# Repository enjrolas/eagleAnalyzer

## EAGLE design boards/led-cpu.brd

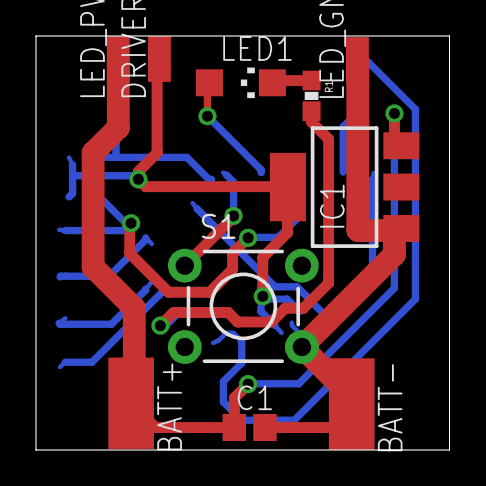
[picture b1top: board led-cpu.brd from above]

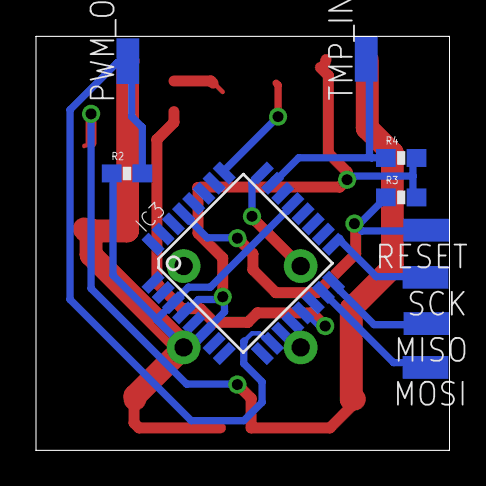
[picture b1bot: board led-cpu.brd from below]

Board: 2 copper layers, 23.0 x 23.0 mm, 20 parts (10 on the bottom side), 13 nets.

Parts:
BATT+: SMD2,54-5,08
BATT-: SMD2,54-5,08
C1: 0.1uF; C0805
DRIVER_PWR: SMD1,27-2,54
IC1: LD117AS50TR; SOT223
IC3: MEGA8-AI; TQFP32-08
LED1: D1; CHIPLED_1206
LED_GND: SMD1,27-2,54
LED_PWR: SMD1,27-2,54
MISO: MISO; SMD1,27-2,54
MOSI: MOSI; SMD1,27-2,54
PWM_OUT: SMD1,27-2,54
R1: 33; 0603-RES
R2, R3: 10k; 0603-RES
R4: 2k7; 0603-RES
RESET: SMD1,27-2,54
S1: TACTILE-PTH
SCK: SCK; SMD1,27-2,54
TMP_IN: SMD1,27-2,54

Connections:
IND_LED_A: IC3.25, LED1.A
IND_LED_B: IC3.13, R1.2
LED_GND: BATT-.1, C1.2, IC1.1, IC3.3, IC3.5, IC3.21, LED_GND.1, R2.1, S1.4
MISO: IC3.16, MISO.1
MOSI: IC3.15, MOSI.1
unnamed: LED1.C, R1.1
unnamed: BATT+.1, C1.1, IC1.3, LED_PWR.1
PWM_OUT: IC3.10, PWM_OUT.1, R2.2
PWR_SW: IC3.24, S1.1
RESET: IC3.29, R3.1, RESET.1
SCK: IC3.17, SCK.1
TMP_IN: IC3.23, R4.1, TMP_IN.1
VCC: DRIVER_PWR.1, IC1.4, IC3.4, IC3.6, R3.2, R4.2

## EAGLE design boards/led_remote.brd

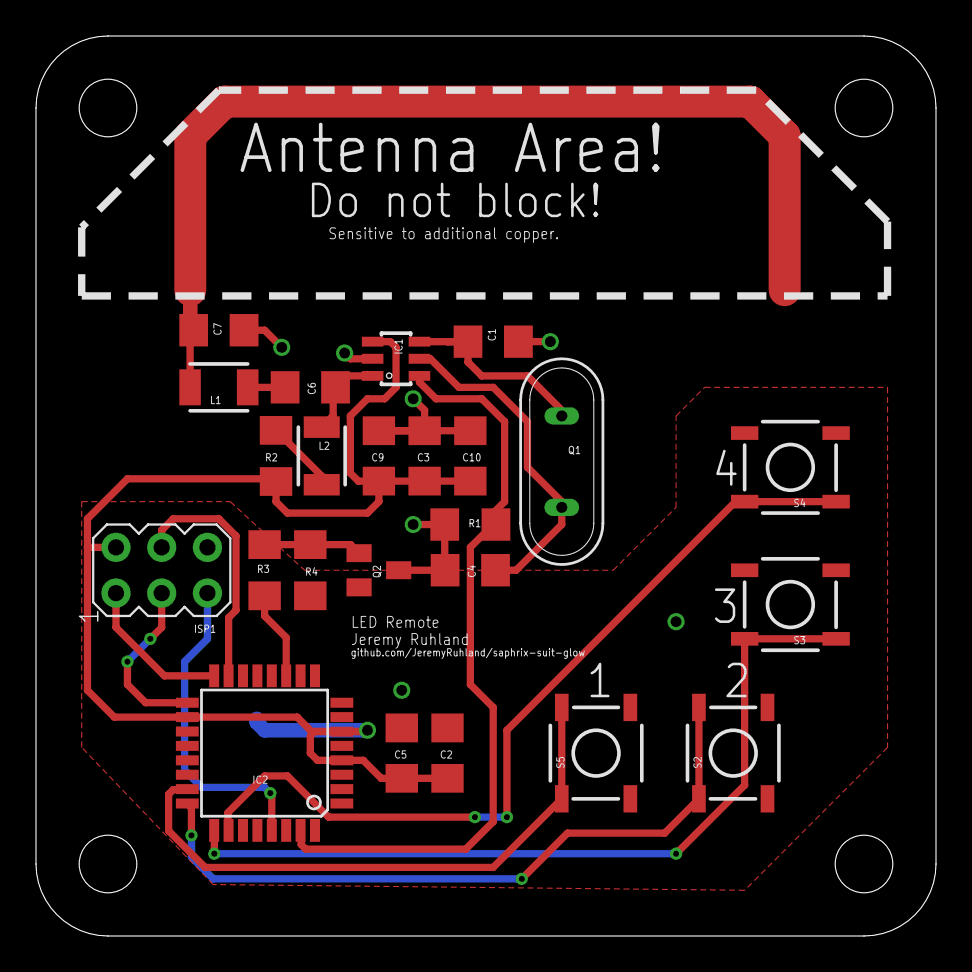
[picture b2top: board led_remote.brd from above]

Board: 2 copper layers, 50.0 x 50.0 mm, 26 parts (1 on the bottom side), 20 nets.

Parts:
C1, C4: 18pf; C1206
C2, C9: 10uf; C1206
C3, C5: 0.1uf; C1206
C6: 12pf; C1206
C7: 4.7pf; C1206
C10: 100pf; C1206
G1: BATTCON_20MM
IC1: MICRF113; SOT23-6
IC2: MEGA8-AI; TQFP32-08
ISP1: AVRISP-6; AVRISP
L1: 1210
L2: 470nh; 1210
PCB2: PCB_DP_SQUARE-5X5; DP5050_V1
Q1: 13.56mhz; QS
Q2: SOT23
R1, R4: 100k; R1206
R2: R1206
R3: 100; R1206
S2, S3, S4, S5: TACTILE_SWITCH_SMD

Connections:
AGND: C1.2, C3.2, C4.2, C7.2, C9.2, C10.2, IC1.2, Q2.3, R1.1
ANT: C7.1, L1.2
GND: C2.2, C5.2, G1.2, IC2.3, IC2.5, IC2.21, ISP1.6, Q2.2, R4.1, S2.3, S2.4, S3.3, S3.4, S4.3, S4.4, S5.3, S5.4
MISO: IC2.16, ISP1.1
MOSI: IC2.15, ISP1.4
unnamed: L2.1, R2.1
unnamed: Q2.1, R3.1, R4.2
unnamed: C1.1, IC1.4, Q1.1
unnamed: C4.1, IC1.5, Q1.2
unnamed: IC2.26, S4.1, S4.2
unnamed: C6.1, IC1.1, L2.2
unnamed: C6.2, L1.1
unnamed: IC2.23, S5.1, S5.2
unnamed: IC2.24, S2.1, S2.2
unnamed: IC2.25, S3.1, S3.2
RST: IC2.29, ISP1.5
SCK: IC2.17, ISP1.3
TX: IC1.6, IC2.31, R1.2
TXPWR: IC2.11, R3.2
VCC: C2.1, C3.1, C5.1, C9.1, C10.1, G1.1, IC1.3, IC2.4, IC2.6, IC2.18, ISP1.2, R2.2

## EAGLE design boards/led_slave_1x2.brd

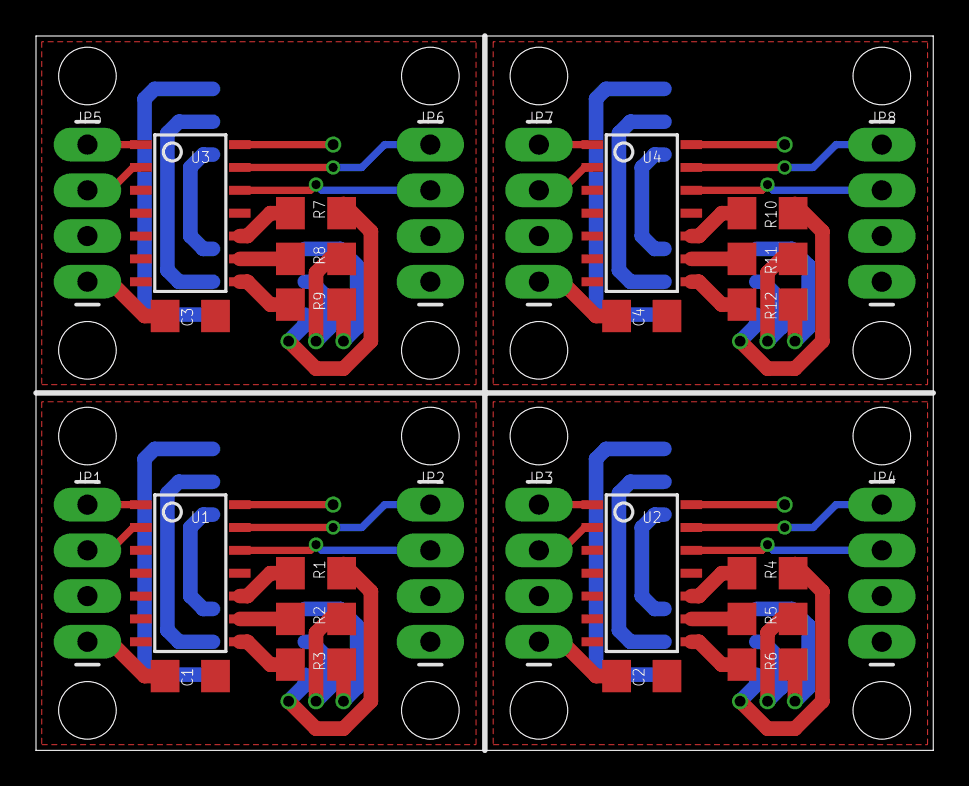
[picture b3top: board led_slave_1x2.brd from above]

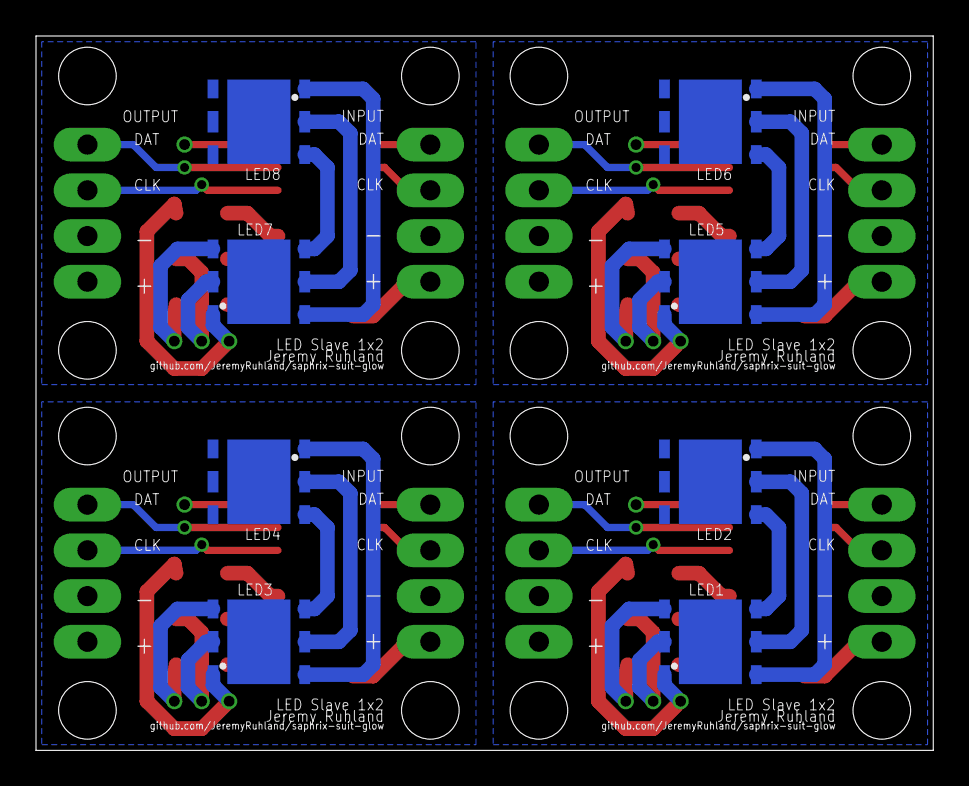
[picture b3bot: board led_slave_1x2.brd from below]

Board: 2 copper layers, 49.8 x 39.7 mm, 36 parts (8 on the bottom side), 60 nets.

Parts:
C1, C2, C3, C4: C1206
JP1, JP2, JP3, JP4, JP5, JP6, JP7, JP8: 1X04_LONGPADS
LED1, LED2, LED3, LED4, LED5, LED6, LED7, LED8: F50360
R1, R2, R3, R4, R5, R6, R7, R8, R9, R10, R11, R12: R1206
U1, U2, U3, U4: WS2801; SOP-14

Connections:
unnamed: JP1.3, U1.2
unnamed: JP1.4, U1.1
unnamed: JP2.4, U1.13
unnamed: JP2.3, U1.12
unnamed: R1.2, U1.10
unnamed: R2.2, U1.9
unnamed: R3.2, U1.8
unnamed: JP4.4, U2.13
unnamed: JP4.3, U2.12
unnamed: LED3.BA, LED4.BC
unnamed: LED1.BC, R3.1
unnamed: LED1.GC, R2.1
unnamed: LED3.GA, LED4.GC
unnamed: LED3.RA, LED4.RC
unnamed: LED1.BA, LED2.BC
unnamed: LED1.GA, LED2.GC
unnamed: LED1.RA, LED2.RC
unnamed: R4.2, U2.10
unnamed: R5.2, U2.9
unnamed: R6.2, U2.8
unnamed: LED1.RC, R1.1
unnamed: LED3.BC, R6.1
unnamed: LED3.GC, R5.1
unnamed: LED3.RC, R4.1
unnamed: JP3.3, U2.2
unnamed: C1.1, JP1.1, JP2.1, LED2.BA, LED2.GA, LED2.RA, U1.14
unnamed: C1.2, JP1.2, JP2.2, U1.4, U1.5, U1.6, U1.7
unnamed: JP3.4, U2.1
unnamed: C2.1, JP3.1, JP4.1, LED4.BA, LED4.GA, LED4.RA, U2.14
unnamed: C2.2, JP3.2, JP4.2, U2.4, U2.5, U2.6, U2.7
unnamed: JP6.4, U3.13
unnamed: JP6.3, U3.12
unnamed: LED5.BA, LED6.BC
unnamed: LED5.GA, LED6.GC
unnamed: LED5.RA, LED6.RC
unnamed: R7.2, U3.10
unnamed: R8.2, U3.9
unnamed: R9.2, U3.8
unnamed: LED5.BC, R9.1
unnamed: LED5.GC, R8.1
unnamed: LED5.RC, R7.1
unnamed: JP5.3, U3.2
unnamed: JP5.4, U3.1
unnamed: C3.1, JP5.1, JP6.1, LED6.BA, LED6.GA, LED6.RA, U3.14
unnamed: C3.2, JP5.2, JP6.2, U3.4, U3.5, U3.6, U3.7
unnamed: JP8.4, U4.13
unnamed: JP8.3, U4.12
unnamed: LED7.BA, LED8.BC
unnamed: LED7.GA, LED8.GC
unnamed: LED7.RA, LED8.RC
unnamed: R10.2, U4.10
unnamed: R11.2, U4.9
unnamed: R12.2, U4.8
unnamed: LED7.BC, R12.1
unnamed: LED7.GC, R11.1
unnamed: LED7.RC, R10.1
unnamed: JP7.3, U4.2
unnamed: JP7.4, U4.1
unnamed: C4.1, JP7.1, JP8.1, LED8.BA, LED8.GA, LED8.RA, U4.14
unnamed: C4.2, JP7.2, JP8.2, U4.4, U4.5, U4.6, U4.7

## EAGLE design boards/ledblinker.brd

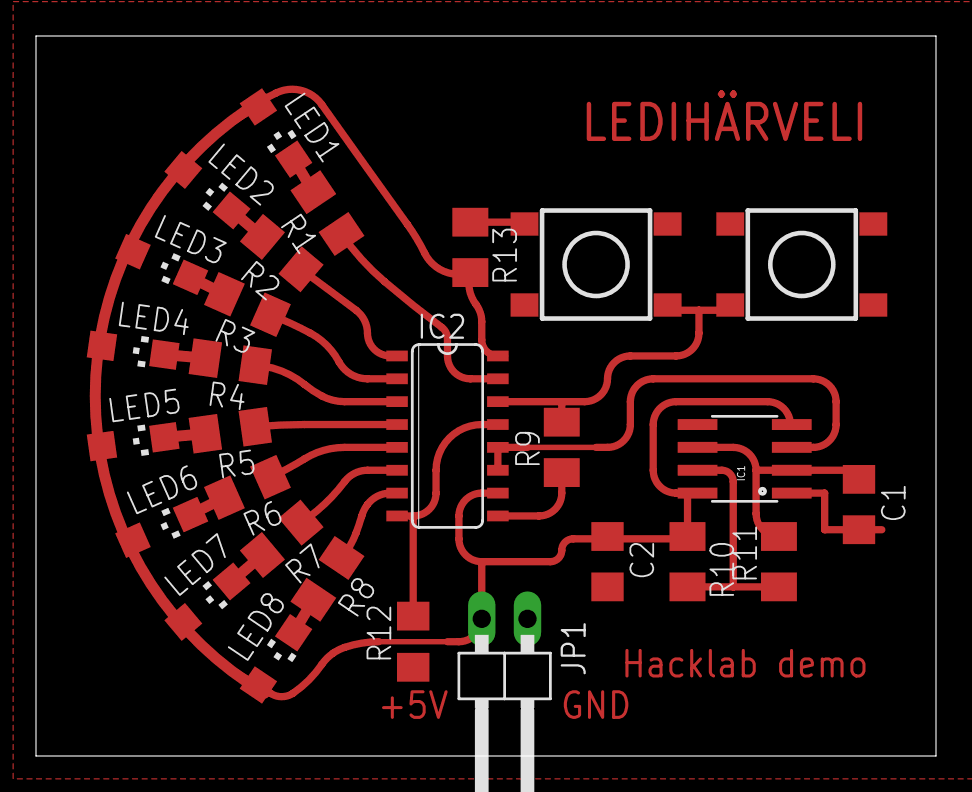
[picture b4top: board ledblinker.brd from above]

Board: 2 copper layers, 50.0 x 40.0 mm, 28 parts (0 on the bottom side), 25 nets.

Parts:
C1, C2: 100nF; C1206
IC1: NE555D; SO08
IC2: 74LS595D; SO16
JP1: 1X02/90
LED1, LED2, LED3, LED4, LED5, LED6, LED7, LED8: CHIPLED_1206
R1, R2, R3, R4, R5, R6, R7, R8: 220; M1206
R9: 22k; M1206
R10: 220k; M1206
R11: 2.2M; M1206
R12: 0R; R1206
R13: 1k; M1206
S1, S3: TACTILE_SWITCH_TALL

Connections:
GND: C1.2, C2.2, IC1.1, JP1.1, R12.1, S1.1, S1.2
unnamed: IC2.15, R1.1
unnamed: IC2.1, R2.1
unnamed: IC2.2, R3.1
unnamed: IC2.3, R4.1
unnamed: IC2.4, R5.1
unnamed: IC2.5, R6.1
unnamed: IC2.6, R7.1
unnamed: IC2.7, R8.1
unnamed: IC2.9, R9.1
unnamed: IC2.14, R9.2, S1.3, S3.1
unnamed: C1.1, IC1.2, IC1.6, R11.2
unnamed: IC1.3, IC2.11, IC2.12
unnamed: IC1.7, R10.2, R11.1
unnamed: LED1.C, R1.2
unnamed: LED2.C, R2.2
unnamed: LED3.C, R3.2
unnamed: LED4.C, R4.2
unnamed: LED5.C, R5.2
unnamed: LED6.C, R6.2
unnamed: LED7.C, R7.2
unnamed: LED8.C, R8.2
unnamed: IC2.8, IC2.13, R12.2
unnamed: R13.1, S3.4
VCC: C2.1, IC1.4, IC1.8, IC2.10, IC2.16, JP1.2, LED1.A, LED2.A, LED3.A, LED4.A, LED5.A, LED6.A, LED7.A, LED8.A, R10.1, R13.2

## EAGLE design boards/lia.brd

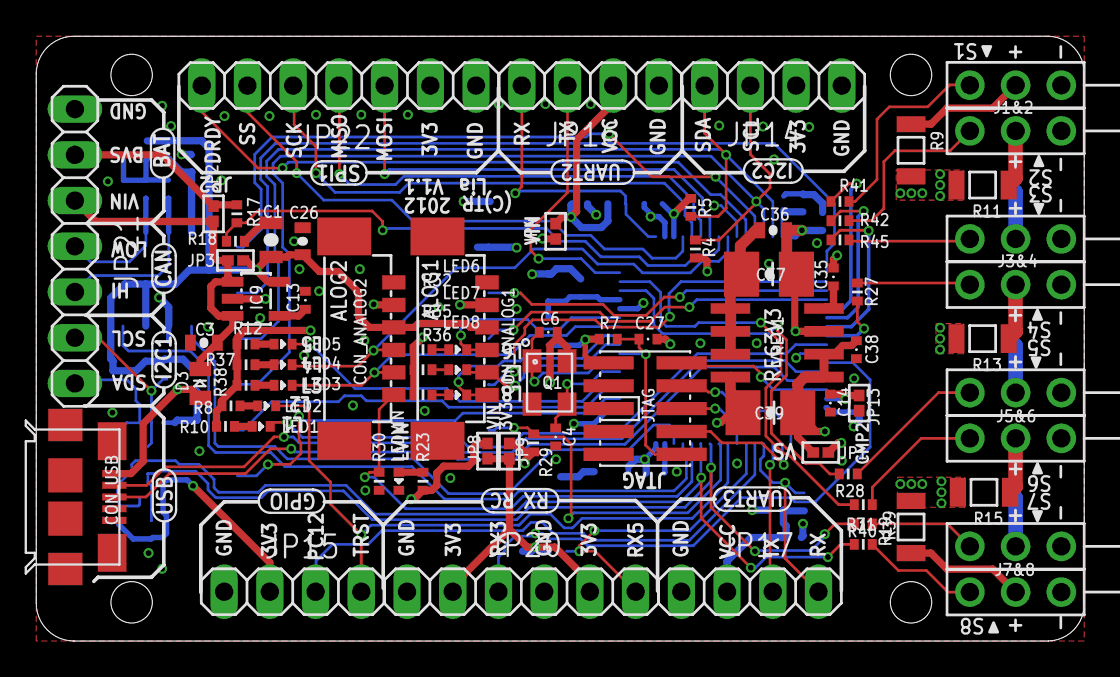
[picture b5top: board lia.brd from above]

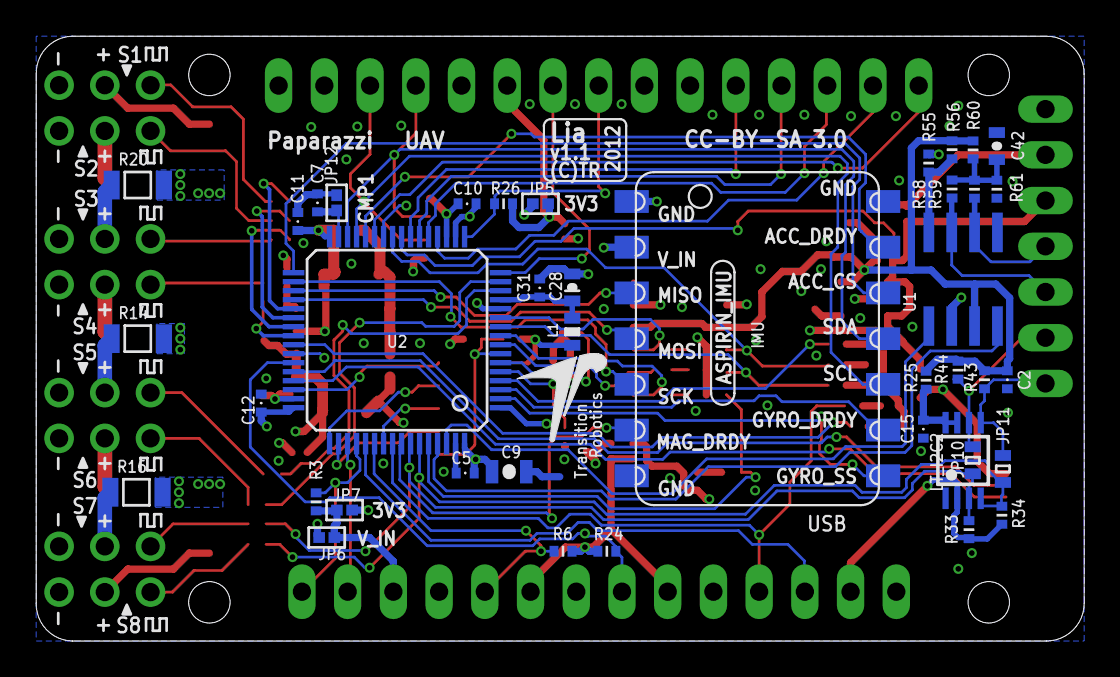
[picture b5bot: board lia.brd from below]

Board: 4 copper layers, 58.2 x 33.6 mm, 122 parts (41 on the bottom side), 98 nets.

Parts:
C1, C9: 4u7; 0805-CAP
C2, C5, C7, C10, C11, C12, C14, C15, C27, C38: 100n; 0402-CAP
C3, C26, C36: 100n; 0603-CAP
C4, C6: 10p; 0402-CAP
C13, C31: 10n; 0402-CAP
C28: 1u; 0603-POL-CAP
C35: 470p; 0402-CAP
C37, C39: 22u; 3528/B
C42: 4n7; 0603-CAP
CON_ANALOG1, CON_ANALOG2: PB-53398-06
CON_USB_MICRO: ZX62-B-5PA
D3: 1N5819; MICROMELF-R
IC9: LP2992 5V; SOT23-5
IMU: ASPIRIN; ASPIRIN_1
J1, J2, J3, J4, J5, J6, J7, J8: CONN_3-1; SIP1X3_100
JP1, JP2, JP3, JP4, JP5, JP6, JP7, JP8, JP9, JP12, JP13: 0/DNP; 0402-SQJMP
JP10, JP11: 0/DNP; 0603-RES
JP14, JP15, JP16, JP17: 1X04
JP20: 1X06
JP21, JP22: 1X07
JTAG: PIN_HDR_EDG_1.27MM_5-2; FTSH-105-DV
L1: 0603-IND
LED1, LED4: RED; 0402-LED
LED2, LED3, LED5: GRN; 0402-LED
LED6, LED7, LED8: BLU; 0402-LED
LEDVIN: GRN; 0402-LED
LT_I2C2: PCA9306DP; TSSOP_B3
Q1: 12Mhz; ABM8
R3, R6, R7, R17, R24, R26, R29, R30: 10k; 0402-RES
R4, R5, R18, R23, R33, R34, R43, R44: 2k2; 0402-RES
R8, R10, R12, R37, R38: 300; 0402-RES
R9, R11, R13, R20: 1R; 1206-RES
R14, R15, R16, R19: 0R; 1206-RES
R25: 200k; 0402-RES
R27, R28, R31, R39, R40, R41, R42, R45: 100R; 0402-RES
R32, R35, R36: 80R; 0402-RES
R55: 0/10k; 0402-RES
R56: 0/DNP; 0402-RES
R58, R59: 60R/DNP; 0402-RES
R60, R61: 4k7/DNP; 0402-RES
U1: MCP2551SN; SO-08
U2: STM32-C-64; LQFP64
U$1: TR-LOGO
VREG1: MIC5209; SOIC8

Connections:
+3V3: C5.P$2, C9.P$1, C10.P$2, C11.P$2, C12.P$2, C36.P$1, C37.+, CON_ANALOG1.2, CON_ANALOG2.2, JP5.P$1, JP7.P$1, JP9.P$1, JP14.2, JP15.2, JP22.2, JTAG.1, L1.P$1, LT_I2C2.2, R4.P$1, R5.P$1, R7.P$2, R8.P$2, R10.P$2, R12.P$2, R29.P$1, R32.P$2, R33.P$2, R34.P$2, R35.P$2, R36.P$2, R37.P$2, R38.P$2, U2.1, U2.19, U2.32, U2.48, U2.64, VREG1.3
+5V: C1.P$1, C2.P$1, C26.P$1, CON_ANALOG1.3, CON_ANALOG2.3, IC9.5, JP3.P$2, R25.P$2, R43.P$2, R44.P$2, R56.P$2, R60.P$1, U1.3
ADC_1: CON_ANALOG1.4, LED6.C, U2.11
ADC_2: CON_ANALOG1.5, LED7.C, U2.8
ADC_3: CON_ANALOG1.6, LED8.C, U2.9
ADC_4: CON_ANALOG2.4, LED4.C, U2.25
ADC_6: CON_ANALOG2.5, LED3.C, U2.10
BOOT0: CON_ANALOG2.6, R30.P$2, U2.60
CAN_CENTER: C42.P$2, R58.P$2, R59.P$1, R60.P$2, R61.P$1
CAN_H: JP21.5, R58.P$1, U1.7
CAN_L: JP21.4, R59.P$2, U1.6
CAN_RX: U1.4, U2.61
CAN_TX: U1.1, U2.62
EXTSPI_DRDY: JP22.7, U2.27
EXTSPI_MISO: JP22.4, U2.22
EXTSPI_MOSI: JP22.3, U2.23
EXTSPI_SCK: JP22.5, U2.21
EXTSPI_SS: JP22.6, U2.20
GND: C1.P$2, C2.P$2, C3.P$2, C4.P$1, C5.P$1, C6.P$2, C7.P$1, C9.P$2, C10.P$1, C11.P$1, C12.P$1, C13.P$2, C14.P$1, C15.P$2, C26.P$2, C27.P$1, C28.-, C31.P$1, C35.P$2, C36.P$2, C37.-, C38.P$2, C39.-, C42.P$1, CON_ANALOG1.1, CON_ANALOG2.1, CON_USB_MICRO.GND_LEFT, CON_USB_MICRO.GND_RIGHT, CON_USB_MICRO.GND_UP_LEFT, CON_USB_MICRO.GND_UP_RIGHT, CON_USB_MICRO.PIN_5, IC9.2, IMU.P$1, IMU.P$7, IMU.P$14, J1.1, J2.1, J3.1, J4.1, J5.1, J6.1, J7.1, J8.1, JP12.P$2, JP13.P$2, JP14.1, JP15.1, JP16.1, JP17.1, JP20.1, JP20.4, JP21.1, JP22.1, JTAG.3, JTAG.5, JTAG.7, JTAG.9, LEDVIN.C, LT_I2C2.1, Q1.P$2, Q1.P$4, R18.P$2, R30.P$1, R55.P$1, R61.P$2, U1.2, U2.12, U2.18, U2.63, VREG1.5, VREG1.6, VREG1.7, VREG1.8
I2C2_SCL: IMU.P$10, JP14.3, R4.P$2, U2.29
I2C2_SDA: IMU.P$11, JP14.4, R5.P$2, U2.30
IMU_ACC_CS: IMU.P$12, U2.33
IMU_ACC_DRDY: IMU.P$13, U2.28
IMU_GYRO_DRDY: IMU.P$9, U2.3
IMU_GYRO_SS: IMU.P$8, U2.2
IMU_MAG_DRDY: IMU.P$6, R29.P$2, U2.57
IMU_SPI_MISO: IMU.P$3, U2.35
IMU_SPI_MOSI: IMU.P$4, U2.36
IMU_SPI_SCK: IMU.P$5, U2.34
JTAG_RST: C27.P$2, JTAG.10, R7.P$1, U2.7
JTAG_TCK: JTAG.4, U2.49
JTAG_TDI: JTAG.8, U2.50
JTAG_TDO: JTAG.6, U2.55
JTAG_TMS: JTAG.2, U2.46
JTAG_TRST: JP15.4, LED2.C, U2.56
LED1: LED1.C, U2.41
LED2: LED5.C, U2.4
LT_I2C1_SCL: JP10.P$2, JP21.6, LT_I2C2.6, R44.P$1
LT_I2C1_SDA: JP11.P$2, JP21.7, LT_I2C2.5, R43.P$1
unnamed: R55.P$2, R56.P$1, U1.8
unnamed: J5.2, R14.P$1
unnamed: J6.2, R15.P$1
unnamed: LED1.A, R10.P$1
unnamed: LED6.A, R32.P$1
unnamed: C13.P$1, IC9.4
unnamed: C35.P$1, VREG1.4
unnamed: C15.P$1, LT_I2C2.7, LT_I2C2.8, R25.P$1
unnamed: LED7.A, R35.P$1
unnamed: LED2.A, R8.P$1
unnamed: LED8.A, R36.P$1
unnamed: LEDVIN.A, R23.P$1
unnamed: LED5.A, R12.P$1
unnamed: LED4.A, R37.P$1
unnamed: LED3.A, R38.P$1
unnamed: J7.2, R16.P$1
unnamed: J8.2, R19.P$1
unnamed: J4.2, R13.P$1
unnamed: J3.2, R20.P$1
unnamed: J2.2, R11.P$1
unnamed: J1.2, R9.P$1
OSC_IN: C4.P$2, Q1.P$3, U2.5
OSC_OUT: C6.P$1, Q1.P$1, U2.6
PC12: JP15.3, U2.53
S1: J1.3, R41.P$1
S2: J2.3, R42.P$1
S3: J3.3, R45.P$1
S4: J4.3, R27.P$1
S5: J5.3, R28.P$1
S6: J6.3, R31.P$1
S7: J7.3, R39.P$1
S8: J8.3, R40.P$1
SERVO_1: R41.P$2, U2.37
SERVO_2: R42.P$2, U2.38
SERVO_3: R45.P$2, U2.39
SERVO_4: R27.P$2, U2.40
SERVO_5: R28.P$2, U2.14
SERVO_6: R31.P$2, U2.15
SERVO_7/I2C1_SCL: JP10.P$1, LT_I2C2.3, R33.P$1, R39.P$2, U2.58
SERVO_8/I2C1_SDA: JP11.P$1, LT_I2C2.4, R34.P$1, R40.P$2, U2.59
SERVO_BUS: JP1.P$1, R9.P$2, R11.P$2, R13.P$2, R14.P$2, R15.P$2, R16.P$2, R19.P$2, R20.P$2
U1_U5_POW: JP8.P$2, JP9.P$2, JP20.2, JP20.5, R6.P$1, R24.P$1
U2_POW: JP4.P$2, JP5.P$2, JP16.2, R26.P$1
U3_POW: JP6.P$2, JP7.P$2, JP17.2, R3.P$1
UART1_RX: JP20.3, R24.P$2, U2.43
UART2_RX: JP16.4, R26.P$2, U2.17
UART2_TX: JP16.3, U2.16
UART3_RX: JP17.4, R3.P$2, U2.52
UART3_TX: JP17.3, U2.51
UART5_RX: JP20.6, R6.P$2, U2.54
USB_DM: CON_USB_MICRO.PIN_2, U2.44
USB_DP: CON_USB_MICRO.PIN_3, U2.45
USB_VBUS: CON_USB_MICRO.PIN_1, D3.A, U2.42
VDDA: C28.+, C31.P$2, L1.P$2, U2.13
VSS1: C7.P$2, JP12.P$1, U2.31
VSS2: C14.P$2, JP13.P$1, U2.47
V_BAT: JP2.P$2, JP21.2, R17.P$1
V_BAT_MEAS: R17.P$2, R18.P$1, U2.24
V_IN: C3.P$1, C38.P$1, C39.+, D3.C, IC9.1, IC9.3, IMU.P$2, JP1.P$2, JP2.P$1, JP3.P$1, JP4.P$1, JP6.P$1, JP8.P$1, JP21.3, R23.P$2, VREG1.1, VREG1.2

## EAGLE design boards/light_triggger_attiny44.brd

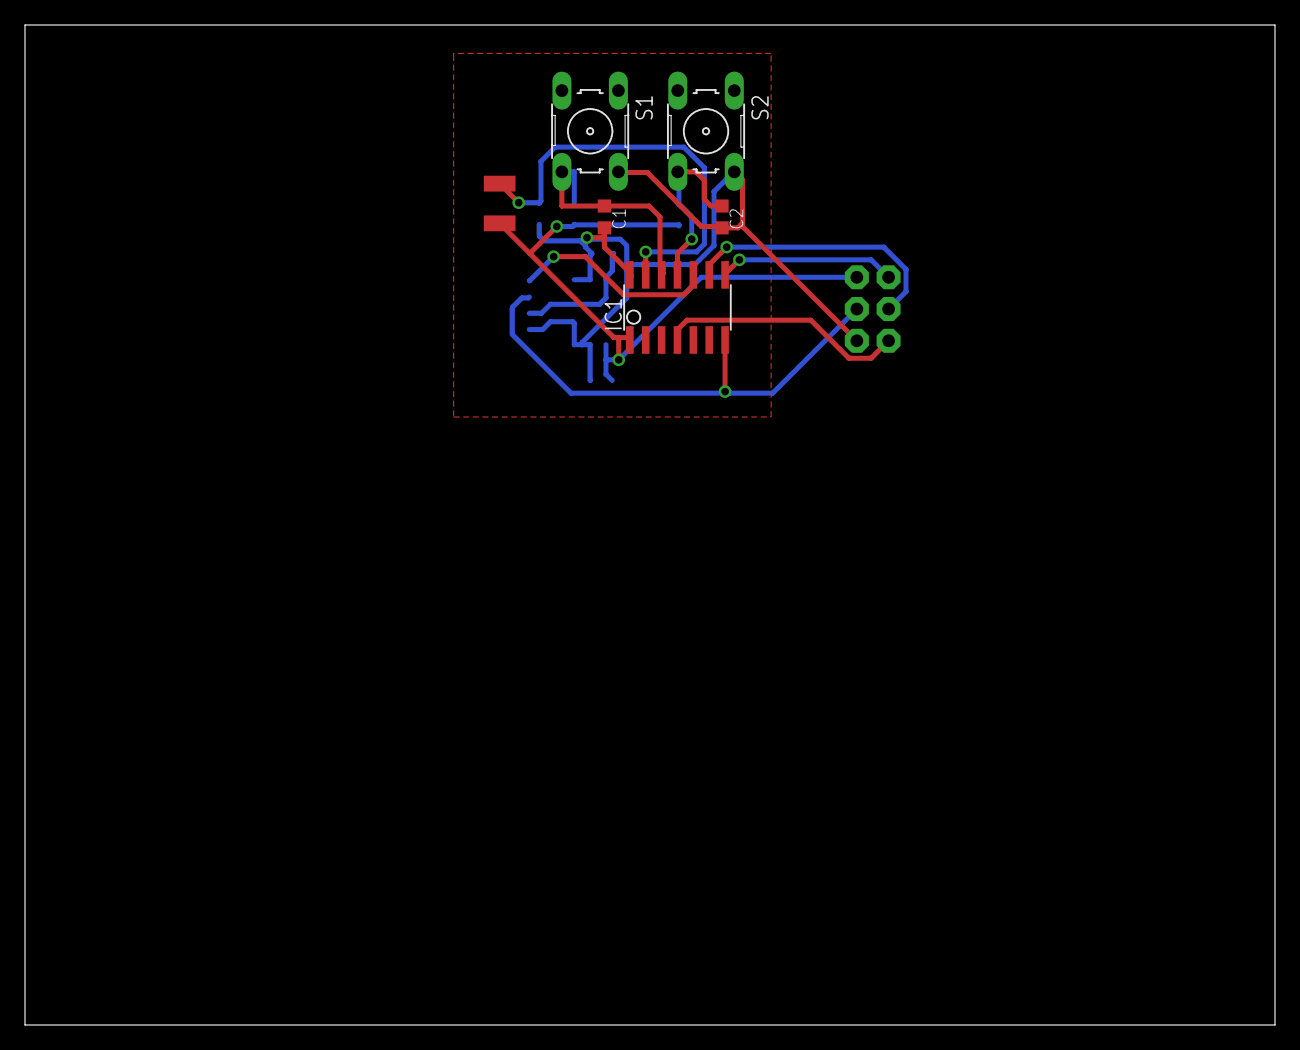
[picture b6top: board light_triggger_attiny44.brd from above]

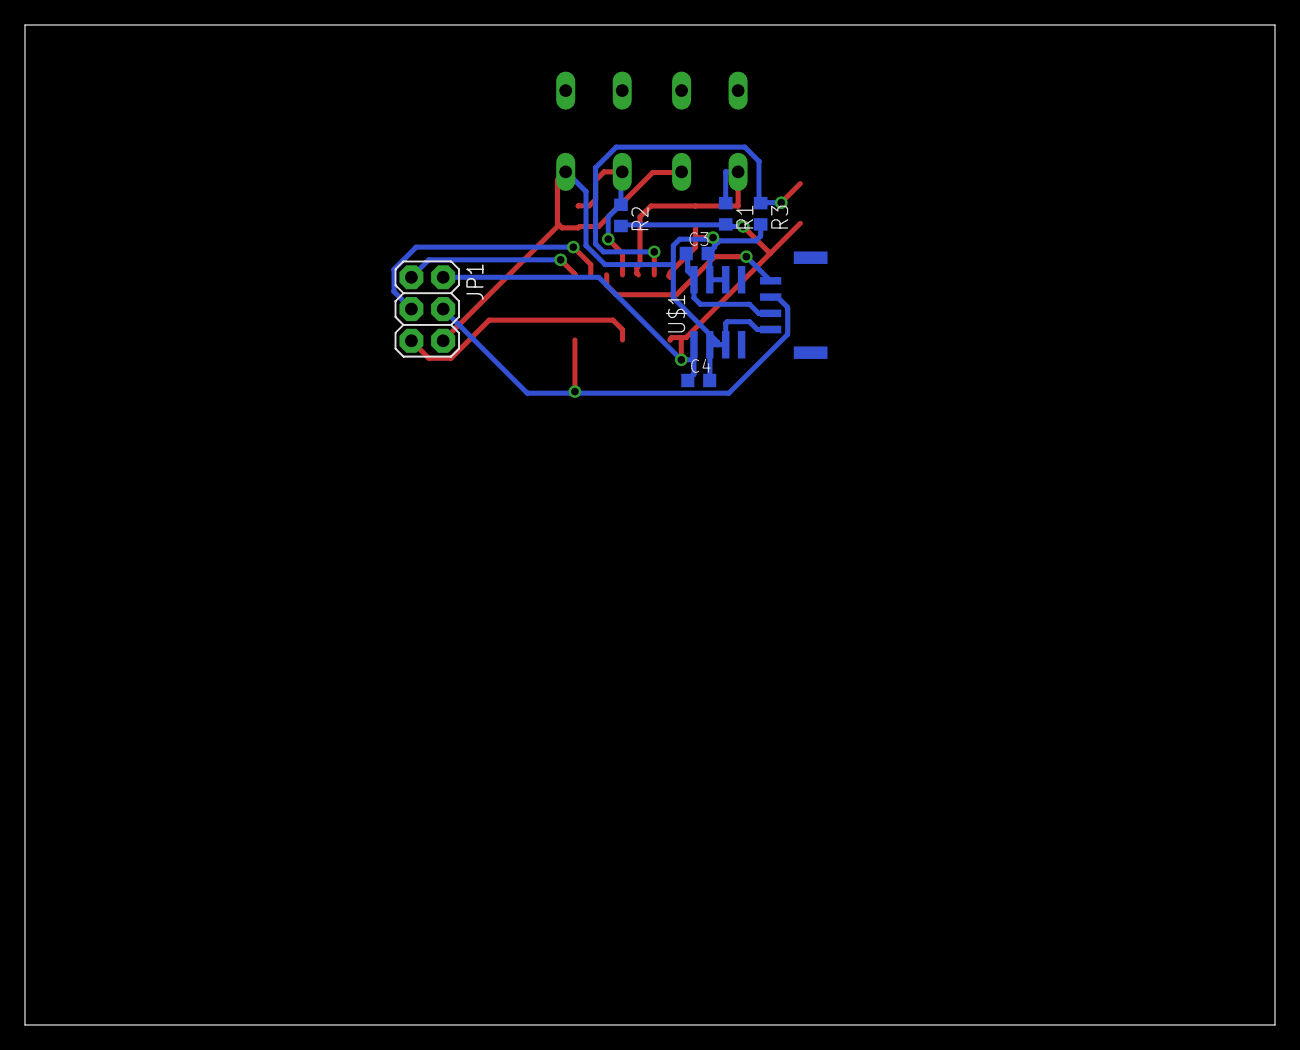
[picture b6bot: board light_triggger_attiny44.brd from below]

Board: 2 copper layers, 100.0 x 80.0 mm, 14 parts (8 on the bottom side), 11 nets.

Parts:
C1, C2, C3, C4: C0603K
IC1: ATTINY24/44/84-SSU; SOIC14
JP1: 2X03
R1, R2, R3: R0603
S1, S2: B3F-10XX
U$1: LM78L05
U$2: 0P525DA; PHOTOTRANSITOR(OP525DA)
U$3: SM04B-GHS-TB

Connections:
GND: C1.2, C2.2, C3.2, C4.2, IC1.14, JP1.6, R3.2, S1.2, S2.2, U$1.2, U$1.3, U$1.6, U$1.7, U$3.GND
MISO: IC1.8, JP1.1
MOSI: IC1.7, JP1.4, U$3.PWMLED
unnamed: IC1.13, R3.1, U$2.P$2
unnamed: IC1.10, U$3.TIMLED
unnamed: C1.1, IC1.12, R1.1, S1.4
unnamed: C2.1, IC1.11, R2.1, S2.4
RST: IC1.4, JP1.5
SCK: IC1.9, JP1.3
VCC: C4.1, IC1.1, JP1.2, R1.2, R2.2, U$1.1, U$2.P$1
VIN: C3.1, U$1.8, U$3.VIN

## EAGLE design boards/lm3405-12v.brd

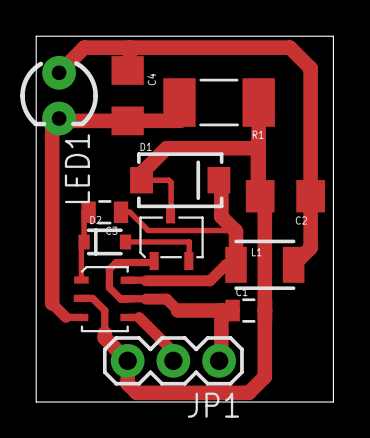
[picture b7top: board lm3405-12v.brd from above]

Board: 2 copper layers, 16.5 x 20.3 mm, 12 parts (0 on the bottom side), 8 nets.

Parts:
C1: 10uF; 0805
C2, C4: 1uF; 1206
C3: 10nF; 0805
D1: SMA-DIODE
D2: SOD-323
JP1: 1X03
L1: 4.7uH; 1210
LED1: LED3MM
R1: 0.2; R2010
U$1: LM3405TSOT-6; TSOT-6
U$2: MAX6100-MAX6107; SOT-23-3

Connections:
GND: C1.2, C2.2, D1.A, JP1.3, R1.1, U$1.2, U$2.3
unnamed: C3.1, D1.C, L1.1, U$1.6
unnamed: C4.2, LED1.K, R1.2, U$1.3
unnamed: C3.2, D2.1, U$1.1
unnamed: C2.1, C4.1, L1.2, LED1.A
unnamed: D2.2, U$2.2
PWM: JP1.2, U$1.4
VCC: C1.1, JP1.1, U$1.5, U$2.1

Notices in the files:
boards/lia.brd:
Licensed under:
http://creativecommons.org/licenses/by-sa/3.0
(C) 2010-2011 Antoine Drouin
(C) 2010-2012 Piotr Esden-Tempski
(C) 2011 Richard Hatano
(C) 2011-2012 Transition Robotics
CC-BY-SA 3.0
parts and their libraries:
sparkfun: Licensing: CC v3.0 Share-Alike You are welcome to use this library for commercial purposes.
